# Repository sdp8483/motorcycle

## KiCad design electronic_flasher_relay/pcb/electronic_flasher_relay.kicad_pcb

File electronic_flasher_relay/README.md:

# Motorcycle Electronic Flasher Relay

*Copy from blog post: https://samueldperry.com/2022/08/13/motorcycle-electronic-flasher-relay/*

To install saddle bags on my 1988 Honda Shadow VT600 motorcycle I needed to relocate the rear indicator lights and since the original indicators were a little worse for wear looking I decided to upgrade to new indicator lights and housings. The motorcycle indicator market has gone mostly LED with almost no aftermarket options with traditional incandescent lights so I decided to upgrade the rear (and eventually the front) indicators to LED.

If you are not aware the stock indicators on my Honda Shadow are flashed using a flasher relay that does not play well with LED indicators. So to install LED indicators and not run into problems such as hyper flashing or the indicators not flashing at all I needed an electronic flasher relay that relies on circuitry and not electromechanics to blink the indicators.

I built the below electronic flasher relay that was heavily inspired by a circuit posted on Instructables, [LED Flasher by scd](https://www.instructables.com/LED-Flasher-automotive-or-motorcycle/). I built upon the design by replacing the BJT to control the lights with a power MOSFET and using a circuit board instead of free forming the circuit. I also used the same connector style and wiring as my original flasher relay so that the unit would be plug and play.

The circuit was assembled on a PCB that was milled using my [3018 Pro Router](https://samueldperry.com/cnc-3018-pro-router/). A section of 1/16″ aluminum was cut as a heatsink for the IRF5210 MOSFET and was pop riveted on with thermal paste between the interface. I made two versions, one with an integrated connector and one with a pigtail connector because I was unsure what would fit my motorcycle best. Then the circuit was placed in a 3D printed enclosure so that it could be potted to protect it from the weather and road grime.

The electronic flasher relay I built will work with both incandescent and LED indicators as well as a mix of the two. The IRF5210 MOSFET is capable of running a 40A load but should be derated to prevent overheating. While designing and building this unit I did find an already built electronic flasher relay for $20 that I ended up buying. It works just as well as the unit I built and also works with both incandescent and LED indicators. I am not sure what unit I will end up using permanently. I worry that the units I built are not fully protected for use in an automotive environment. I may have to put one of my units through some stress testing to see if I can trust it for the long term before installing it in the motorcycle.

For more motorcycle related projects check out my [blog](https://samueldperry.com/motorcycle/).

## Directory Outline
- [`~/pcb/`](pcb) is for KiCAD design files. The schematic, pcb layout, BOM, and GERBER files can be found here.
- [`~/enclosure/`](enclosure) is for mechanical CAD design files for the enclosure or box.

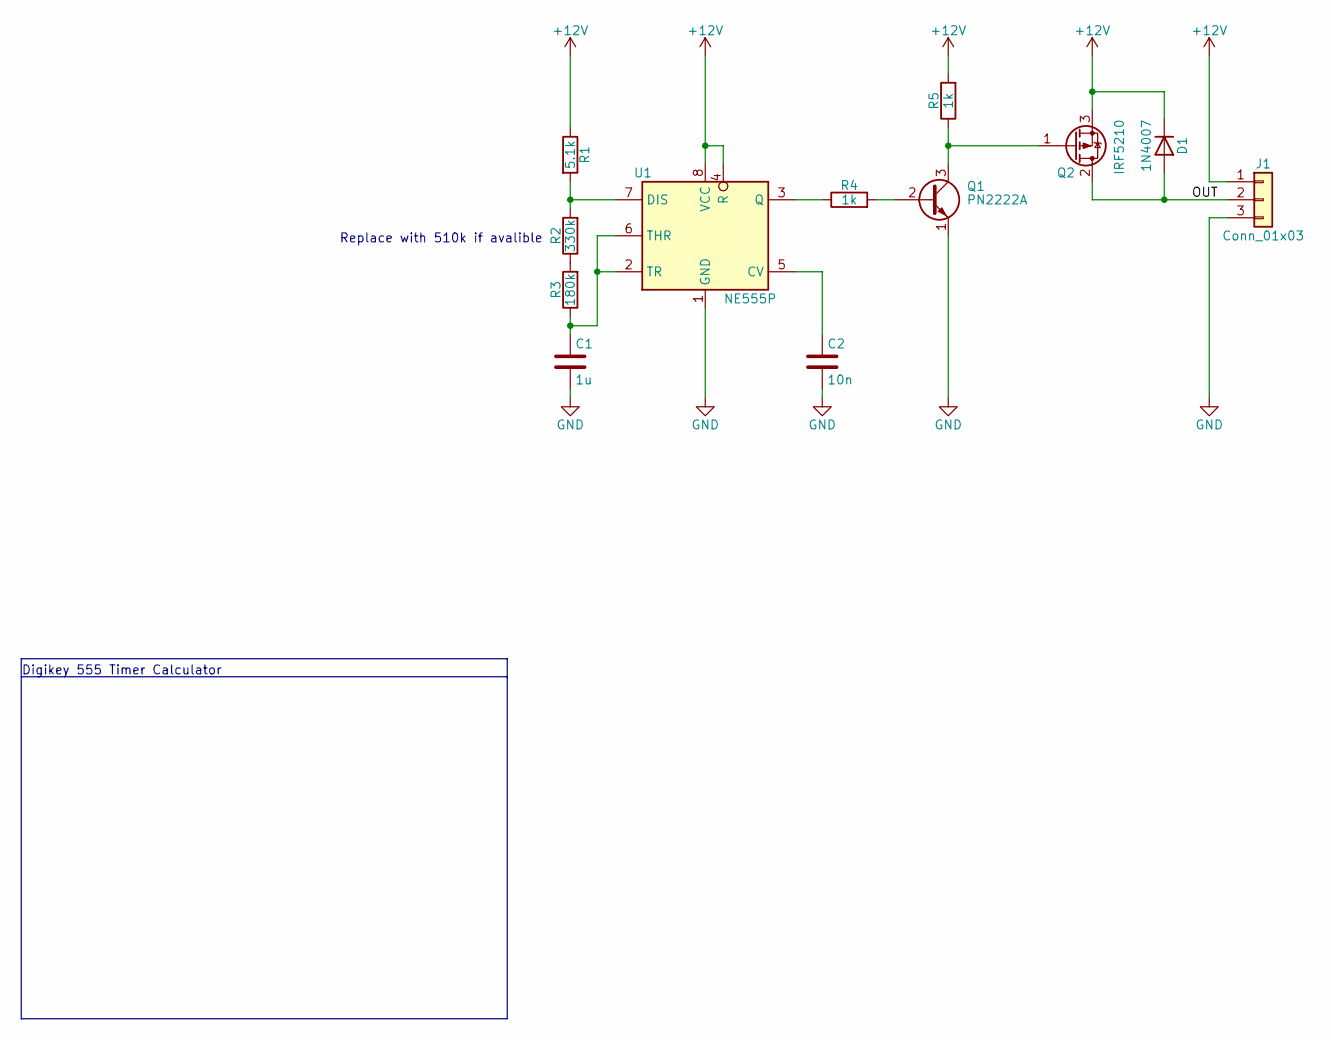
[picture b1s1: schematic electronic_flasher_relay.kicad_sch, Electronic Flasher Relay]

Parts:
C1: 1u; C_1206_3216Metric_Pad1.33x1.80mm_HandSolder
C2: 10n; C_0805_2012Metric_Pad1.18x1.45mm_HandSolder
D1: 1N4007; D_DO-41_SOD81_P10.16mm_Horizontal
J1: Conn_01x03; SolderWire-2.5sqmm_1x03_P7.2mm_D2.4mm_OD3.6mm
Q1: PN2222A; TO-92_Inline_Wide
Q2: IRF5210; TO-220-3_Vertical
R1: 5.1k; R_Axial_DIN0207_L6.3mm_D2.5mm_P10.16mm_Horizontal
R2: 330k; R_Axial_DIN0207_L6.3mm_D2.5mm_P10.16mm_Horizontal
R3: 180k; R_Axial_DIN0207_L6.3mm_D2.5mm_P10.16mm_Horizontal
R4, R5: 1k; R_Axial_DIN0207_L6.3mm_D2.5mm_P10.16mm_Horizontal
U1: NE555P; DIP-8_W7.62mm

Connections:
+12V: D1.1 (K), J1.1, Q2.3 (S), R1.1, R5.2, U1.4 (R), U1.8 (VCC)
/OUT: D1.2 (A), J1.2, Q2.2 (D)
GND: C1.2, C2.2, J1.3, Q1.1 (E), U1.1 (GND)
unnamed: C1.1, R3.1, U1.2 (TR), U1.6 (THR)
unnamed: C2.1, U1.5 (CV)
unnamed: Q1.2 (B), R4.2
unnamed: Q1.3 (C), Q2.1 (G), R5.1
unnamed: R1.2, R2.2, U1.7 (DIS)
unnamed: R2.1, R3.2
unnamed: R4.1, U1.3 (Q)

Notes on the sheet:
Digikey 555 Timer Calculator
Replace with 510k if avalible

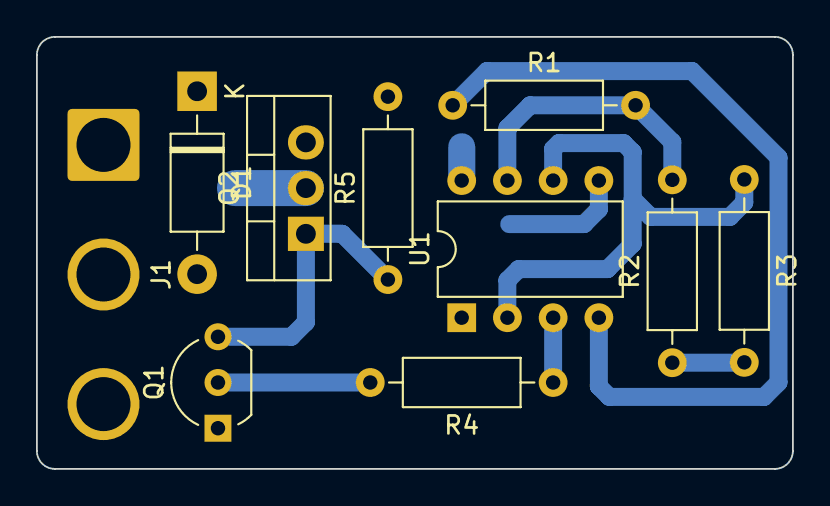
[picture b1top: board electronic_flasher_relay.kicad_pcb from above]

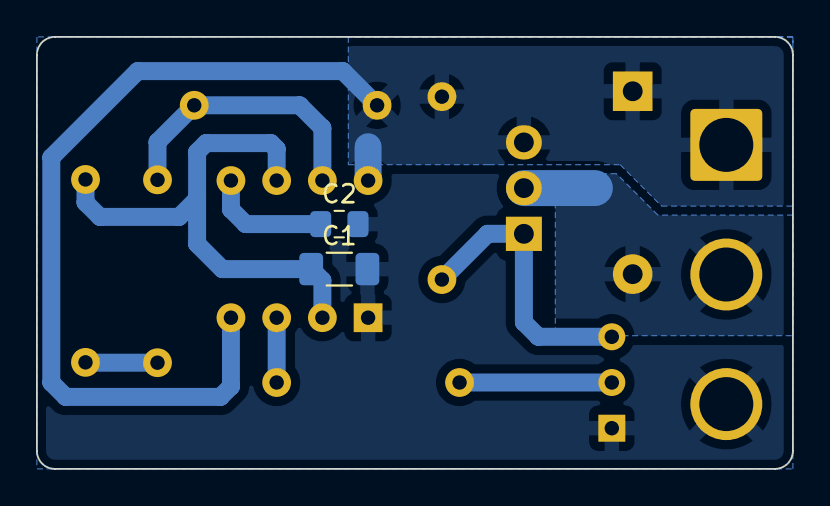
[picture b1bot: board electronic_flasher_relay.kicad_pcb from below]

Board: 2 copper layers, 42.0 x 24.0 mm, 12 parts (2 on the bottom side), 10 nets.

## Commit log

2022-07-29 init commit
    merge electronic_flasher_relay
2022-07-31 init commit
2022-08-01 change resistor values
2022-08-01 add schema image
2022-08-01 more photos
2022-08-01 add output diode
2022-08-04 remove bottom radius
2022-08-07 v2 fork mount
2022-08-07 export for 3d printing
2022-08-07 square mounting tabs
2022-08-13 remove fw dir, there is no firmware
2022-08-19 create epoxy plunger
